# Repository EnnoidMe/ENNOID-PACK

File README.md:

Related ENNOID projects:
  - [BMS](https://github.com/EnnoidMe/ENNOID-BMS)

# ENNOID-PACK

This project aims to create a scalable & modular lithium-ion battery packs based on cylindrical cell format.

## Features:

- Cylindrical cells
- Vertical cells with cooling plate on one side & a cells-PCB on the other side for cells connections.
- No wire assembly with cells-PCB directly connected to ENNOID-BMS slave board for voltages & temperatures monitoring
- Modules can be stacked in parallels & series
- ISOSPI communication toward ENNOID-BMS master board
- 3D printable plastic case

Each module has an ENNOID-BMS slave board mounted for balancing. 

For a complete battery pack system, master board with 12V power supply, contactors & current sensor are integrated in the separate "Penthouse box" 

Available for order:

https://www.ennoid.me/battery

View this project on [CADLAB.io](https://cadlab.io/project/1988).

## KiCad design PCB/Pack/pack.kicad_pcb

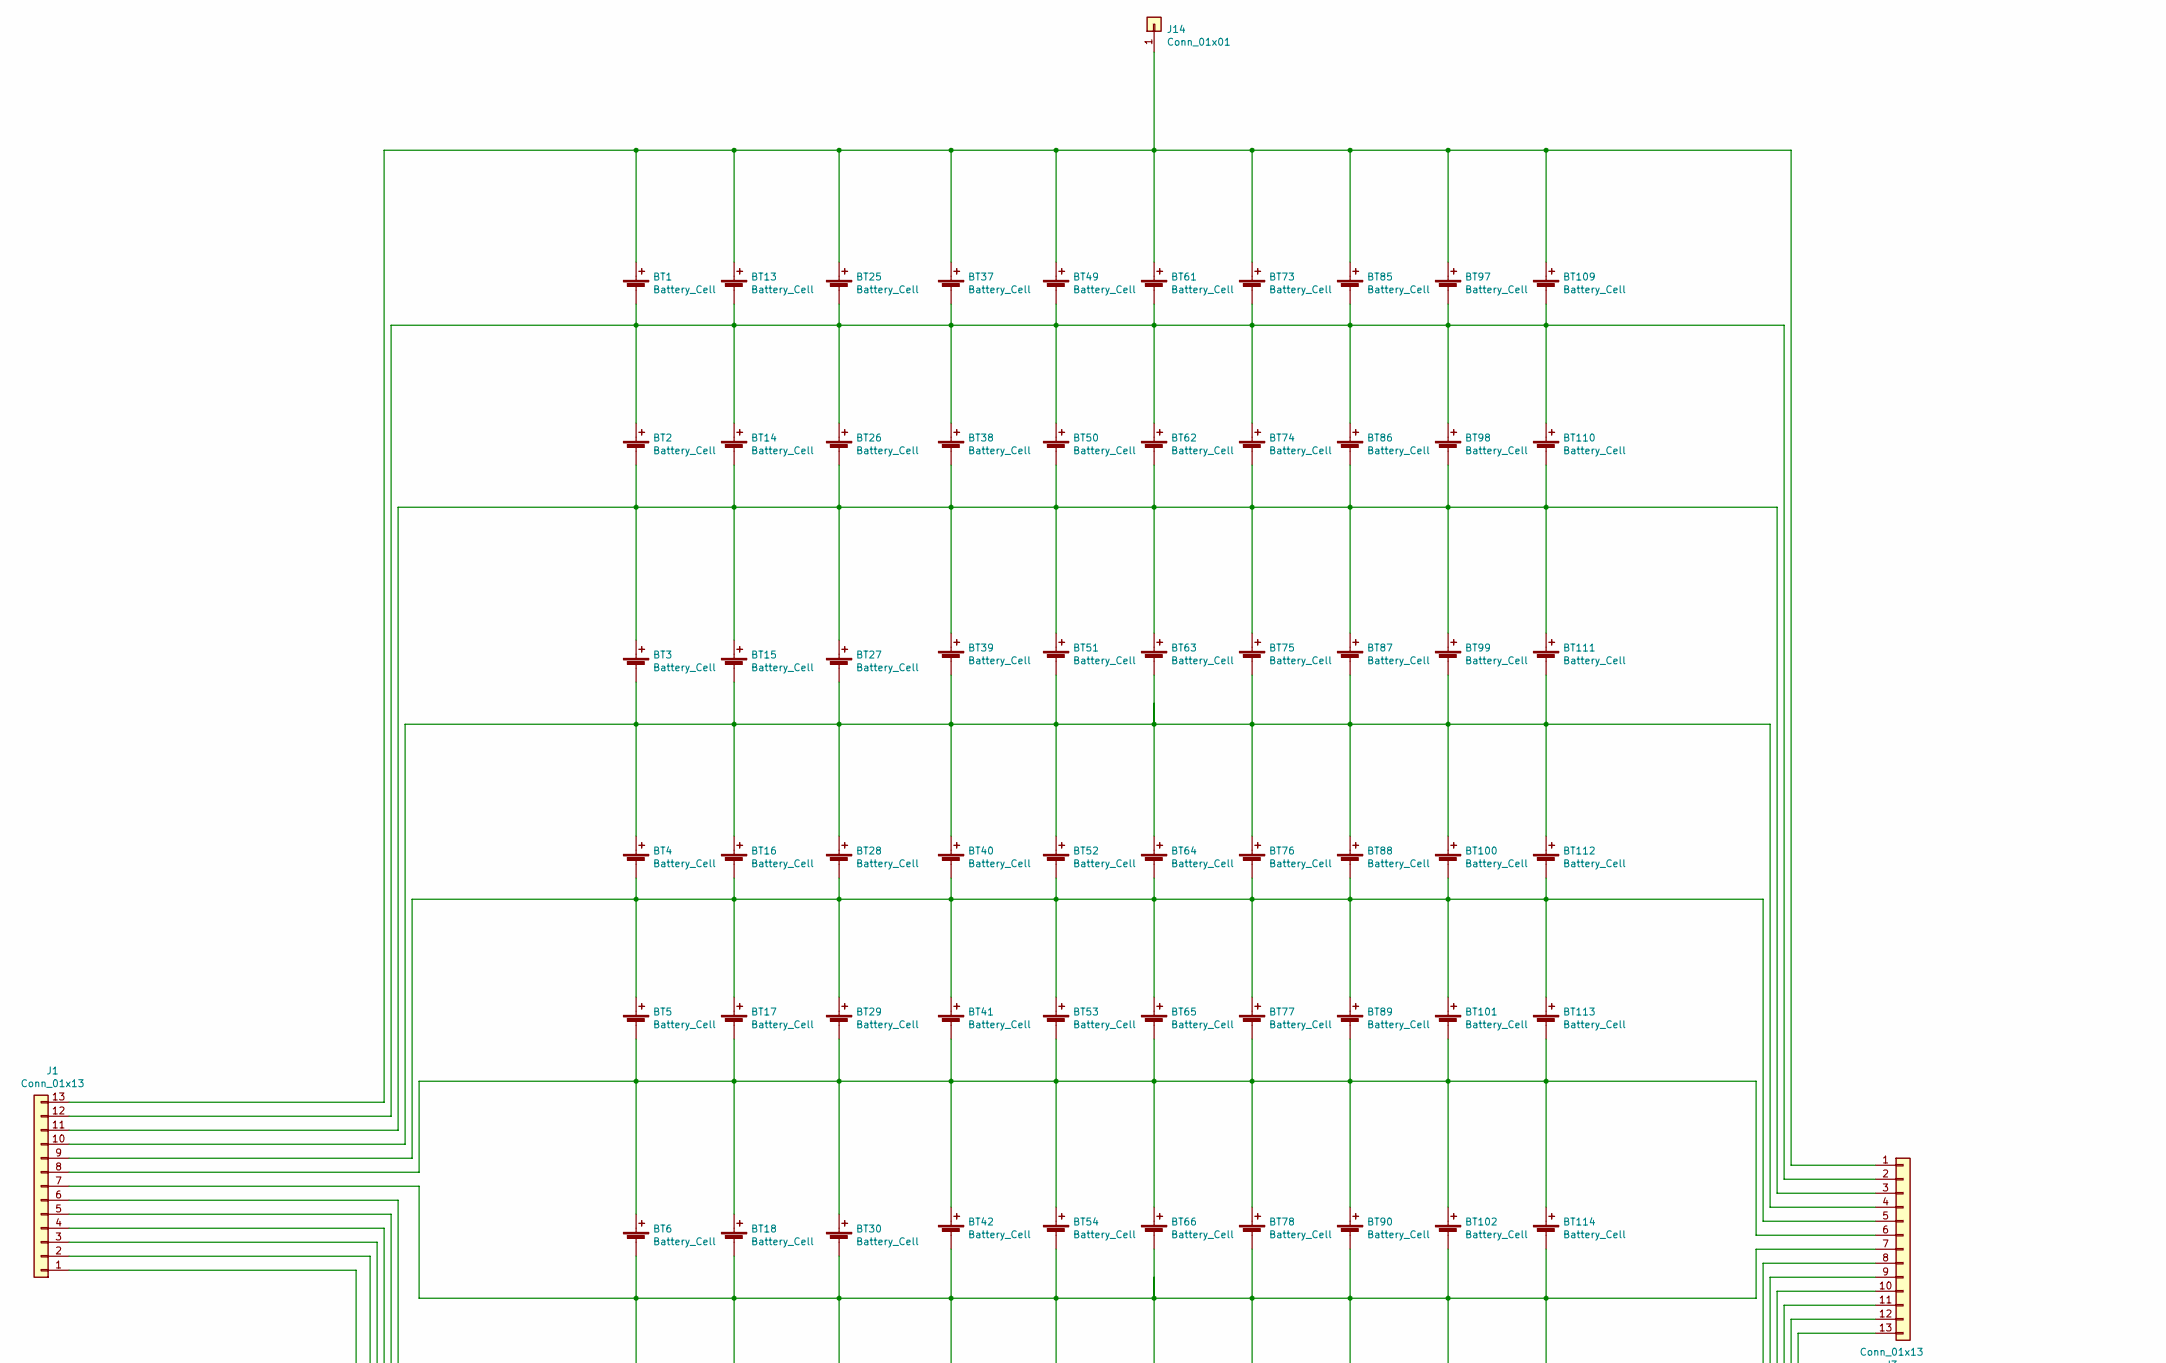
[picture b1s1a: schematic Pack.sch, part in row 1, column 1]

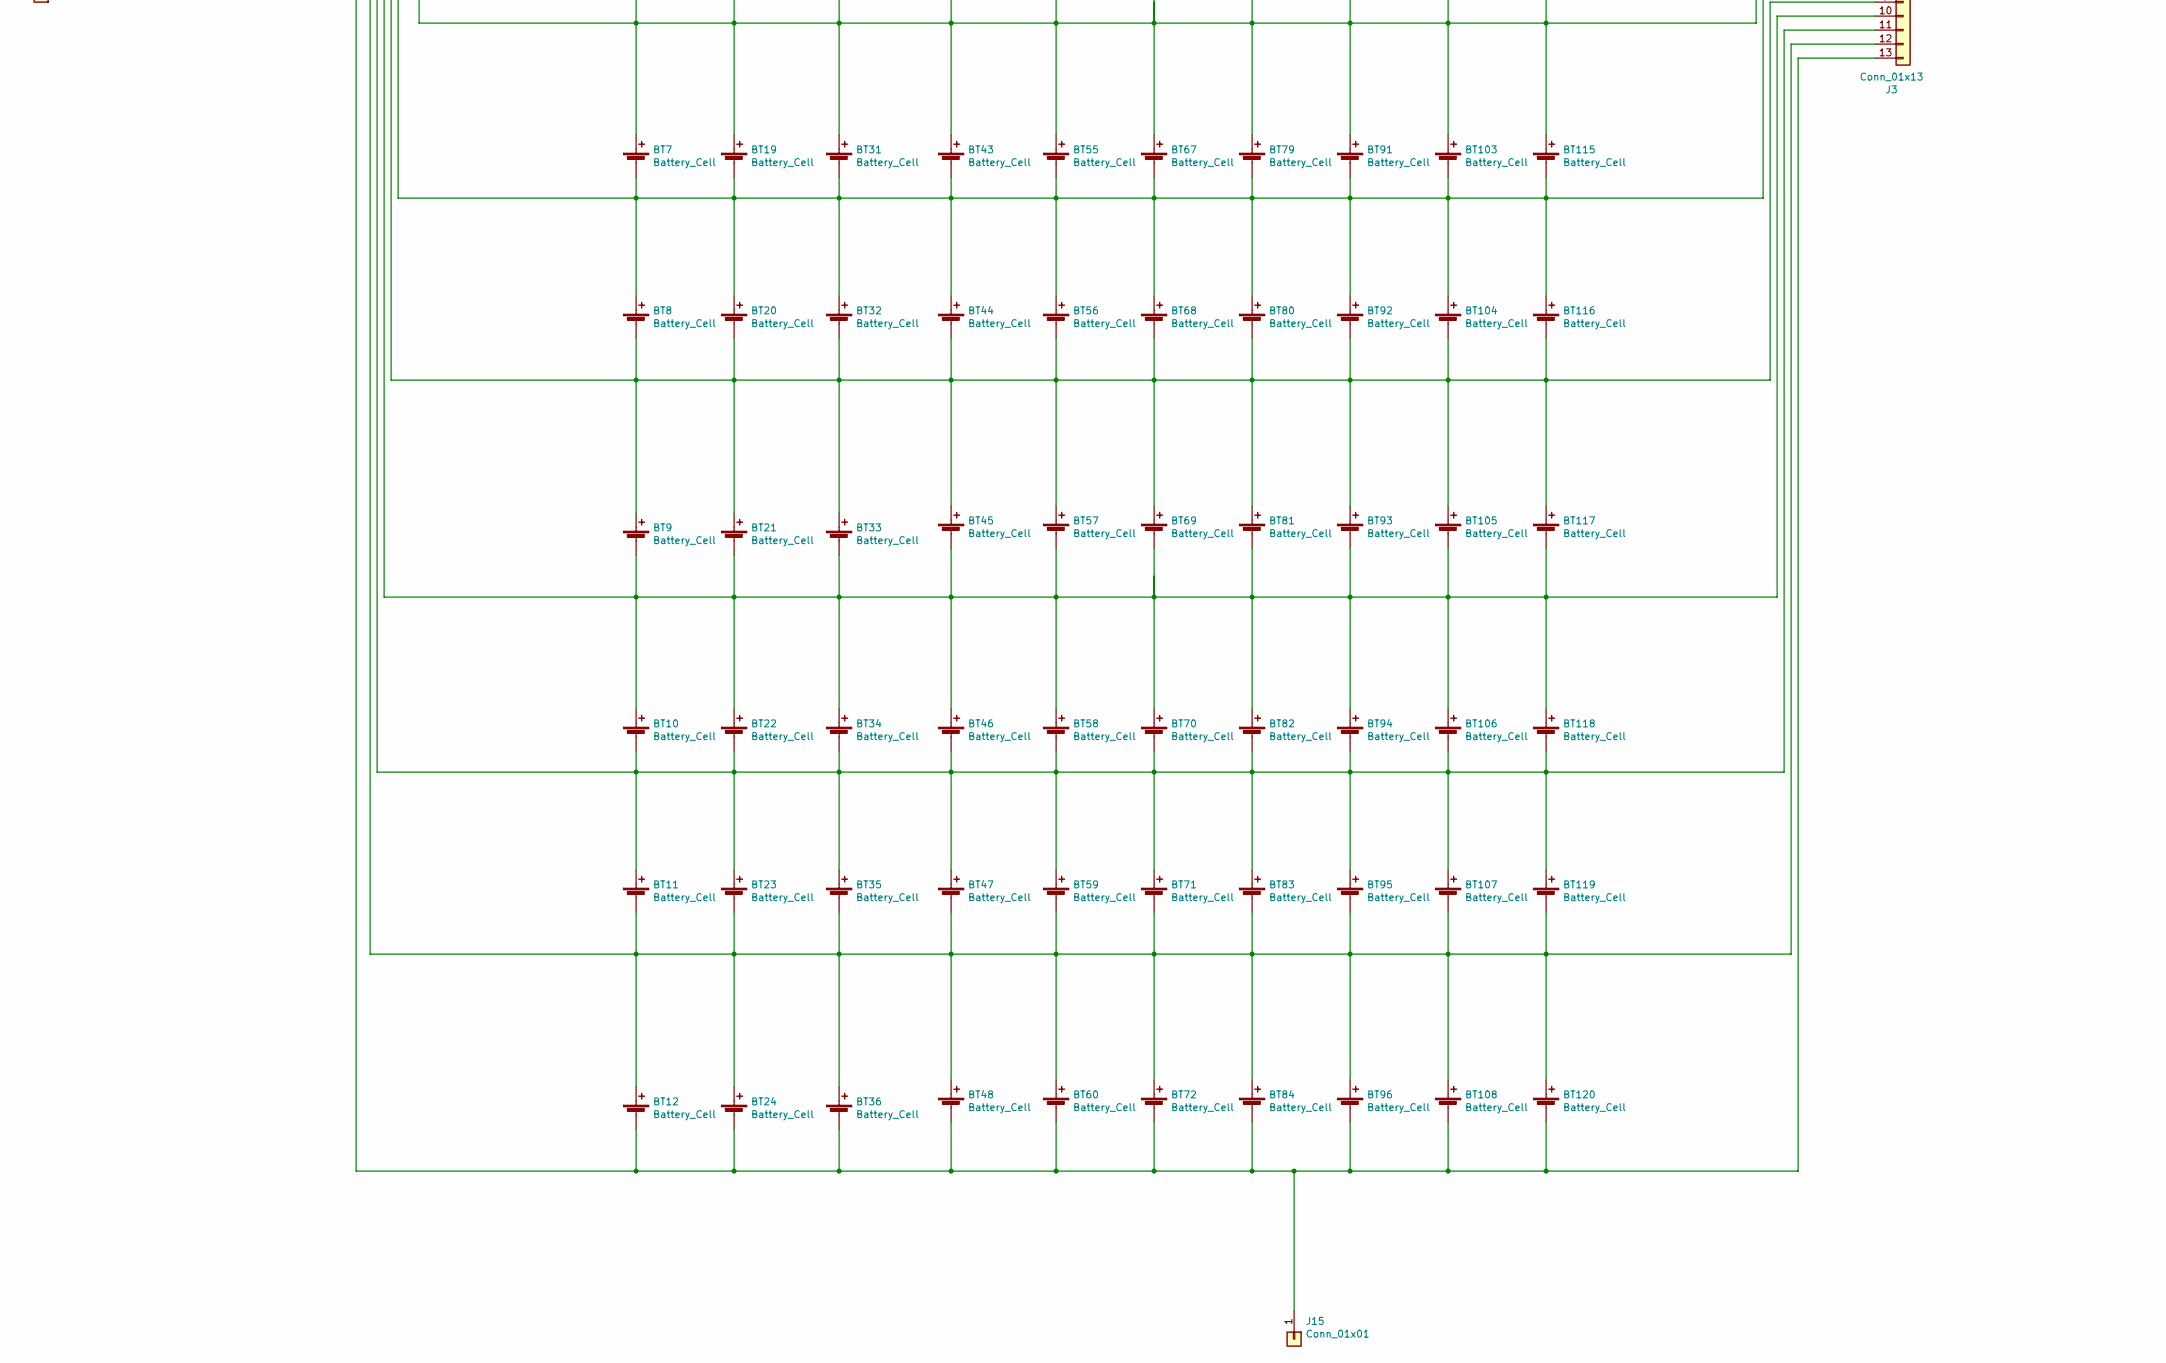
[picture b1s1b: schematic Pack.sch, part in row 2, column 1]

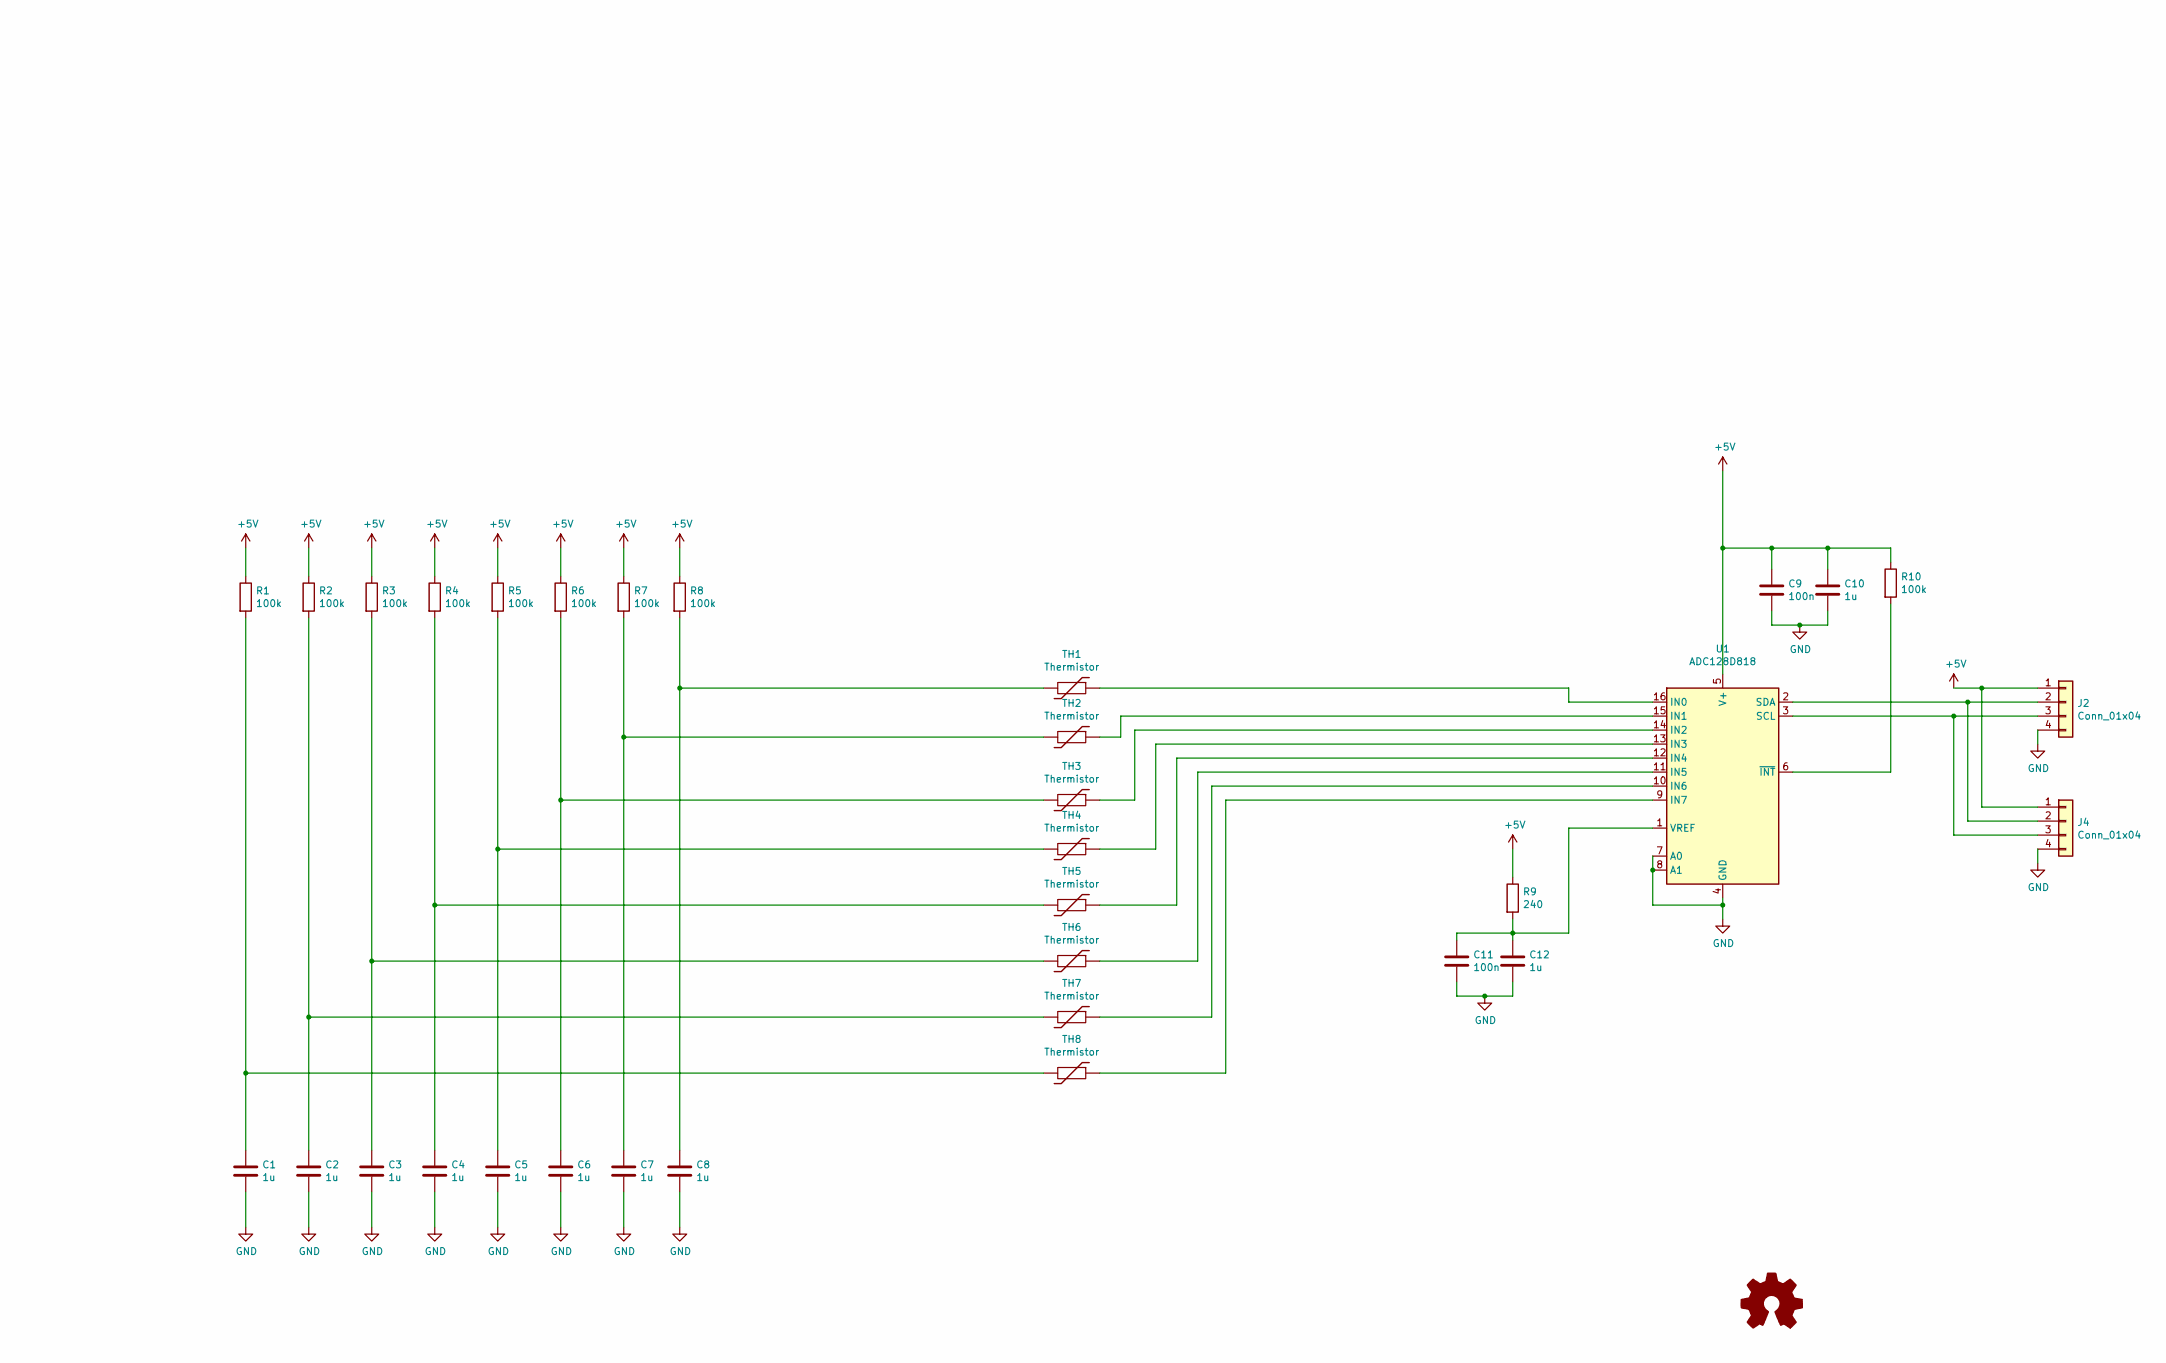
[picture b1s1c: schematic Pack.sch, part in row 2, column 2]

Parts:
BT1, BT2, BT3, BT4, BT5, BT6, BT7, BT8, BT9, BT10, BT11, BT12, BT13, BT14, BT15, BT16, BT17, BT18, BT19, BT20, BT21, BT22, BT23, BT24, BT25, BT26, BT27, BT28, BT29, BT30, BT31, BT32, BT33, BT34, BT35, BT36, BT37, BT38, BT39, BT40, BT41, BT42, BT43, BT44, BT45, BT46, BT47, BT48, BT49, BT50, BT51, BT52, BT53, BT54, BT55, BT56, BT57, BT58, BT59, BT60, BT61, BT62, BT63, BT64, BT65, BT66, BT67, BT68, BT69, BT70, BT71, BT72, BT73, BT74, BT75, BT76, BT77, BT78, BT79, BT80, BT81, BT82, BT83, BT84, BT85, BT86, BT87, BT88, BT89, BT90, BT91, BT92, BT93, BT94, BT95, BT96, BT97, BT98, BT99, BT100, BT101, BT102, BT103, BT104, BT105, BT106, BT107, BT108, BT109, BT110, BT111, BT112, BT113, BT114, BT115, BT116, BT117, BT118, BT119, BT120: Battery_Cell; 18650
C1, C2, C3, C4, C5, C6, C7, C8, C10, C12: 1u; C_0603_HandSoldering
C9, C11: 100n; C_0603_HandSoldering
J1: Conn_01x13; Pin_Header_Straight_1x13_Pitch2.54mm
J2: Conn_01x04; Molex_KK-6410-04_04x2.54mm_Straight
J3: Conn_01x13; Molex_KK-6410-13_13x2.54mm_Straight
J4: Conn_01x04; Pin_Header_Straight_1x04_Pitch2.54mm
J14, J15: Conn_01x01; Pack
LOGO1: Logo_Open_Hardware_Small; ENNOID-LOGO
R1, R2, R3, R4, R5, R6, R7, R8, R10: 100k; R_0603_HandSoldering
R9: 240; R_0603_HandSoldering
TH1, TH2, TH3, TH4, TH5, TH6, TH7, TH8: Thermistor; R_0805_HandSoldering
U1: ADC128D818; TSSOP-16_4.4x5mm_Pitch0.65mm

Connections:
+5V: C9.1, C10.1, J2.1, J4.1, R1.1, R2.1, R3.1, R4.1, R5.1, R6.1, R7.1, R8.1, R9.1, R10.1, U1.5 (V+)
GND: C1.2, C2.2, C3.2, C4.2, C5.2, C6.2, C7.2, C8.2, C9.2, C10.2, C11.2, C12.2, J2.4, J4.4, U1.4 (GND), U1.7 (A0), U1.8 (A1)
unnamed: BT1.1 (+), BT13.1 (+), BT25.1 (+), BT37.1 (+), BT49.1 (+), BT61.1 (+), BT73.1 (+), BT85.1 (+), BT97.1 (+), BT109.1 (+), J1.13, J3.1, J14.1
unnamed: BT1.2 (-), BT2.1 (+), BT13.2 (-), BT14.1 (+), BT25.2 (-), BT26.1 (+), BT37.2 (-), BT38.1 (+), BT49.2 (-), BT50.1 (+), BT61.2 (-), BT62.1 (+), BT73.2 (-), BT74.1 (+), BT85.2 (-), BT86.1 (+), BT97.2 (-), BT98.1 (+), BT109.2 (-), BT110.1 (+), J1.12, J3.2
unnamed: BT9.2 (-), BT10.1 (+), BT21.2 (-), BT22.1 (+), BT33.2 (-), BT34.1 (+), BT45.2 (-), BT46.1 (+), BT57.2 (-), BT58.1 (+), BT69.2 (-), BT70.1 (+), BT81.2 (-), BT82.1 (+), BT93.2 (-), BT94.1 (+), BT105.2 (-), BT106.1 (+), BT117.2 (-), BT118.1 (+), J1.4, J3.10
unnamed: BT10.2 (-), BT11.1 (+), BT22.2 (-), BT23.1 (+), BT34.2 (-), BT35.1 (+), BT46.2 (-), BT47.1 (+), BT58.2 (-), BT59.1 (+), BT70.2 (-), BT71.1 (+), BT82.2 (-), BT83.1 (+), BT94.2 (-), BT95.1 (+), BT106.2 (-), BT107.1 (+), BT118.2 (-), BT119.1 (+), J1.3, J3.11
unnamed: BT3.2 (-), BT4.1 (+), BT15.2 (-), BT16.1 (+), BT27.2 (-), BT28.1 (+), BT39.2 (-), BT40.1 (+), BT51.2 (-), BT52.1 (+), BT63.2 (-), BT64.1 (+), BT75.2 (-), BT76.1 (+), BT87.2 (-), BT88.1 (+), BT99.2 (-), BT100.1 (+), BT111.2 (-), BT112.1 (+), J1.10, J3.4
unnamed: BT4.2 (-), BT5.1 (+), BT16.2 (-), BT17.1 (+), BT28.2 (-), BT29.1 (+), BT40.2 (-), BT41.1 (+), BT52.2 (-), BT53.1 (+), BT64.2 (-), BT65.1 (+), BT76.2 (-), BT77.1 (+), BT88.2 (-), BT89.1 (+), BT100.2 (-), BT101.1 (+), BT112.2 (-), BT113.1 (+), J1.9, J3.5
unnamed: BT5.2 (-), BT6.1 (+), BT17.2 (-), BT18.1 (+), BT29.2 (-), BT30.1 (+), BT41.2 (-), BT42.1 (+), BT53.2 (-), BT54.1 (+), BT65.2 (-), BT66.1 (+), BT77.2 (-), BT78.1 (+), BT89.2 (-), BT90.1 (+), BT101.2 (-), BT102.1 (+), BT113.2 (-), BT114.1 (+), J1.8, J3.6
unnamed: BT6.2 (-), BT7.1 (+), BT18.2 (-), BT19.1 (+), BT30.2 (-), BT31.1 (+), BT42.2 (-), BT43.1 (+), BT54.2 (-), BT55.1 (+), BT66.2 (-), BT67.1 (+), BT78.2 (-), BT79.1 (+), BT90.2 (-), BT91.1 (+), BT102.2 (-), BT103.1 (+), BT114.2 (-), BT115.1 (+), J1.7, J3.7
unnamed: BT7.2 (-), BT8.1 (+), BT19.2 (-), BT20.1 (+), BT31.2 (-), BT32.1 (+), BT43.2 (-), BT44.1 (+), BT55.2 (-), BT56.1 (+), BT67.2 (-), BT68.1 (+), BT79.2 (-), BT80.1 (+), BT91.2 (-), BT92.1 (+), BT103.2 (-), BT104.1 (+), BT115.2 (-), BT116.1 (+), J1.6, J3.8
unnamed: BT8.2 (-), BT9.1 (+), BT20.2 (-), BT21.1 (+), BT32.2 (-), BT33.1 (+), BT44.2 (-), BT45.1 (+), BT56.2 (-), BT57.1 (+), BT68.2 (-), BT69.1 (+), BT80.2 (-), BT81.1 (+), BT92.2 (-), BT93.1 (+), BT104.2 (-), BT105.1 (+), BT116.2 (-), BT117.1 (+), J1.5, J3.9
unnamed: BT11.2 (-), BT12.1 (+), BT23.2 (-), BT24.1 (+), BT35.2 (-), BT36.1 (+), BT47.2 (-), BT48.1 (+), BT59.2 (-), BT60.1 (+), BT71.2 (-), BT72.1 (+), BT83.2 (-), BT84.1 (+), BT95.2 (-), BT96.1 (+), BT107.2 (-), BT108.1 (+), BT119.2 (-), BT120.1 (+), J1.2, J3.12
unnamed: BT12.2 (-), BT24.2 (-), BT36.2 (-), BT48.2 (-), BT60.2 (-), BT72.2 (-), BT84.2 (-), BT96.2 (-), BT108.2 (-), BT120.2 (-), J1.1, J3.13, J15.1
unnamed: BT2.2 (-), BT3.1 (+), BT14.2 (-), BT15.1 (+), BT26.2 (-), BT27.1 (+), BT38.2 (-), BT39.1 (+), BT50.2 (-), BT51.1 (+), BT62.2 (-), BT63.1 (+), BT74.2 (-), BT75.1 (+), BT86.2 (-), BT87.1 (+), BT98.2 (-), BT99.1 (+), BT110.2 (-), BT111.1 (+), J1.11, J3.3
unnamed: C1.1, R1.2, TH8.2
unnamed: C2.1, R2.2, TH7.2
unnamed: C3.1, R3.2, TH6.2
unnamed: C4.1, R4.2, TH5.2
unnamed: C5.1, R5.2, TH4.2
unnamed: C6.1, R6.2, TH3.2
unnamed: C7.1, R7.2, TH2.2
unnamed: C8.1, R8.2, TH1.2
unnamed: C11.1, C12.1, R9.2, U1.1 (VREF)
unnamed: J2.2, J4.2, U1.2 (SDA)
unnamed: J2.3, J4.3, U1.3 (SCL)
unnamed: R10.2, U1.6 (~INT)
unnamed: TH1.1, U1.16 (IN0)
unnamed: TH2.1, U1.15 (IN1)
unnamed: TH3.1, U1.14 (IN2)
unnamed: TH4.1, U1.13 (IN3)
unnamed: TH5.1, U1.12 (IN4)
unnamed: TH6.1, U1.11 (IN5)
unnamed: TH7.1, U1.10 (IN6)
unnamed: TH8.1, U1.9 (IN7)

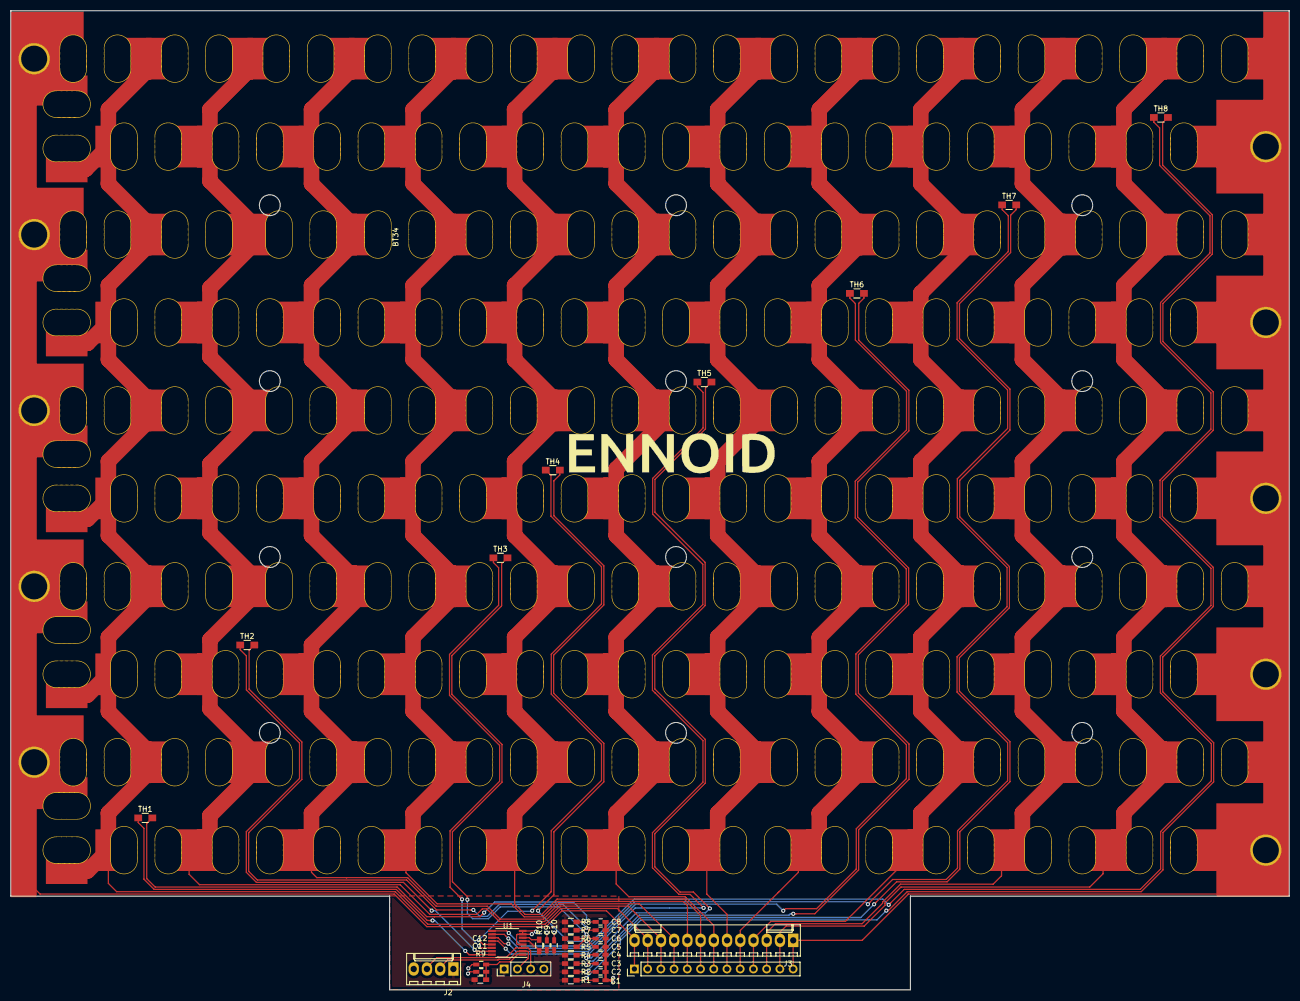
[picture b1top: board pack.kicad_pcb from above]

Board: 2 copper layers, 245.4 x 187.9 mm, 158 parts (0 on the bottom side), 35 nets.

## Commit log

2019-02-01 init commit
2019-02-01 pack schematic & pcb
2019-02-02 pack update
2019-02-03 Pack completed
2019-02-03 readme
2019-02-05 minor stuff
2019-02-08 gerber
2019-02-16 small changes
2019-03-04 no more on board fuses
2019-03-04 cad modif
2019-03-05 block changes
2019-03-06 block
2019-03-06 small change
2019-03-06 nothing
2019-03-06 conflict removed
2019-03-06 traces changed
2019-03-06 Traces
2019-03-08 PCB major changes
2019-03-08 Final version
2019-03-09 New pic
2019-05-02 Major update 12S10P
    3dprintable casing for 12S10P 1.5kWh
2019-05-03 small changes to top pcb
2019-05-03 minor changes
2019-06-02 cad update
2019-07-17 Backlink to CADLAB.io has been added.
2019-07-17 Updated design
2019-07-24 HV pack update
2019-07-29 Major pack change. Penthouse box added
2019-11-06 Basic update
2019-11-06 Readme update
